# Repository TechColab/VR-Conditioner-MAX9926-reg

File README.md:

I hope this helps anyone interested.
Anyway, I've done what I can & it's now ready for many eye-balls.

Phill

### 2021-02-23
I have not made & tested this design but it is barely changed from the manufacrurers data sheets or other designs.
If you make & test it then please advise.

I'm new to KiCAD so I don't know how to do some things.  Such as how to have an 8-pin set of holes without a 3D chip sitting in it.
Or how to do an 8-pin header in the shape & pin count order of a chip.

### 2021-02-24
Changed version number to 3.5 so that it reflects relative cronology from previous design.
Renamed this from Notes.txt to README.md & corrected the date above.
Added Comments to schematic, inc. single-sided design allowing 'Letter' postage!
Updated BOM in schematic to reflect readily available parts found on OctoPart.

### 2021-04-22
Goal: give the left 6 passive components some space from the edge.
Increace size/power of some SMT resistors where suggested.
Re-route COUT1 from DIP.8 to SIL.4 in green so no signal traces are by the edge.
Shift right 5 components slightly right.
Shift DIP, chip & hidden cap slightly right.
Shift left 6 components slightly right.
Re-route left 6 components to avoid side swapping.
Ensure GND plane encircles everything with a via in each corner.
Tidy with some symetry.
Ensure all 'thin' traces are 0.20mm (up from 0.16)

### 2021-08-16
Move to it's own project to reflect that Speeduino main project has dropped all VRs.
Re-applied logical resistor numbering.  Bumped schematic v to 3.7 to match PCB.

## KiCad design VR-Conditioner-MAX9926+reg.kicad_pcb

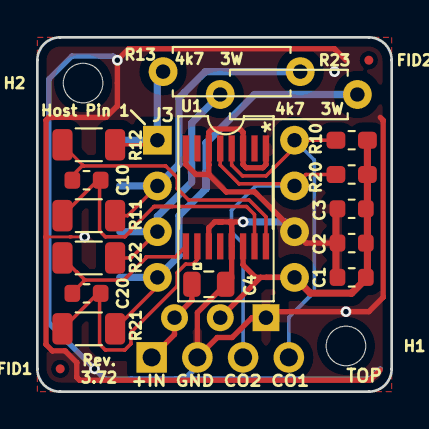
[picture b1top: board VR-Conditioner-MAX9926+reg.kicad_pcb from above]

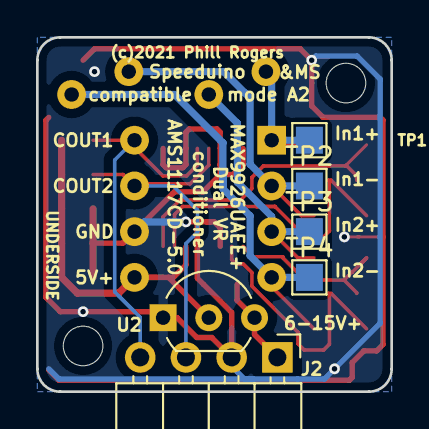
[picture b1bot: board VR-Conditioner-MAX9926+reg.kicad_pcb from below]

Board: 2 copper layers, 19.7 x 19.7 mm, 26 parts (6 on the bottom side), 13 nets.

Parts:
C1: 10n; C_0603_1608Metric
C2: 100n; C_0603_1608Metric
C3: 1u; C_0603_1608Metric
C4: 10u; C_0805_2012Metric
C10, C20: 1n; C_0603_1608Metric
FID1, FID2: Fiducial; Fiducial_0.5mm_Mask1mm
H1, H2: MountingHole; MountingHole_2.2mm_M2
J2: Edge; PinHeader_1x04_P2.54mm_Horizontal
J3: 8-pin header; DIP-8_W7.62mm
R10, R20: 1k; R_0603_1608Metric_Pad1.05x0.95mm_HandSolder
R11, R12, R21, R22: 10k; R_1206_3216Metric
R13, R23: 4.7k; R_Axial_DIN0207_L6.3mm_D2.5mm_P7.62mm_Horizontal
TP1, TP2, TP3, TP4: TP; TestPoint_Pad_1.5x1.5mm
U1: MAX9926UAEE+; MAX9926UAEE&plus_
U2: AMS1117CD-5.0; TO-92_Inline_Wide

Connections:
+12V: C4.1, J2.1, U2.3 (VI)
/COUT1: J2.4, J3.8, R10.2, U1.4 (COUT1)
/COUT2: J2.3, J3.7, R20.2, U1.5 (COUT2)
GND: C1.2, C2.2, C3.2, C4.2, J2.2, J3.6, U1.1 (INT_THRS1), U1.3 (BIAS1), U1.6 (BIAS2), U1.8 (INT_THRS2), U1.11 (GND), U1.13 (ZERO_EN), U2.1 (GND)
unnamed: C10.1, R12.1, U1.16 (IN1+)
unnamed: C10.2, R11.1, U1.15 (IN1-)
unnamed: C20.1, R21.1, U1.10 (IN2-)
unnamed: C20.2, R22.1, U1.9 (IN2+)
unnamed: J3.1, R12.2, R13.1, TP1.1
unnamed: J3.2, R11.2, R13.2, TP2.2 (1)
unnamed: J3.3, R22.2, R23.1, TP3.3 (1)
unnamed: J3.4, R21.2, R23.2, TP4.4 (1)
VCC: C1.1, C2.1, C3.1, J3.5, R10.1, R20.1, U1.14 (VCC), U2.2 (VO)

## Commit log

2021-08-16 v3.7
2021-08-16 more readme typos
2021-08-16 bump thin trace to 0.2mm
2022-08-07 Improve silk screen labeling & ground plane. Added solder pads.
2022-08-07 Remove silk text from test point solder pads.
2023-01-22 v3.74 corrects channel 1 polarity, improves silkscreen & makes soldering of PTH bits easier.
    Polarity in previous version not critical as everyone seems to try their pick-up each way anyhow.

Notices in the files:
VR-Conditioner-MAX9926+reg.kicad_pcb:
(c)2021 Phill Rogers @ TechColab.co.je
parts and their libraries:
Copyright 2016 Accelerated Designs. All rights reserved.
